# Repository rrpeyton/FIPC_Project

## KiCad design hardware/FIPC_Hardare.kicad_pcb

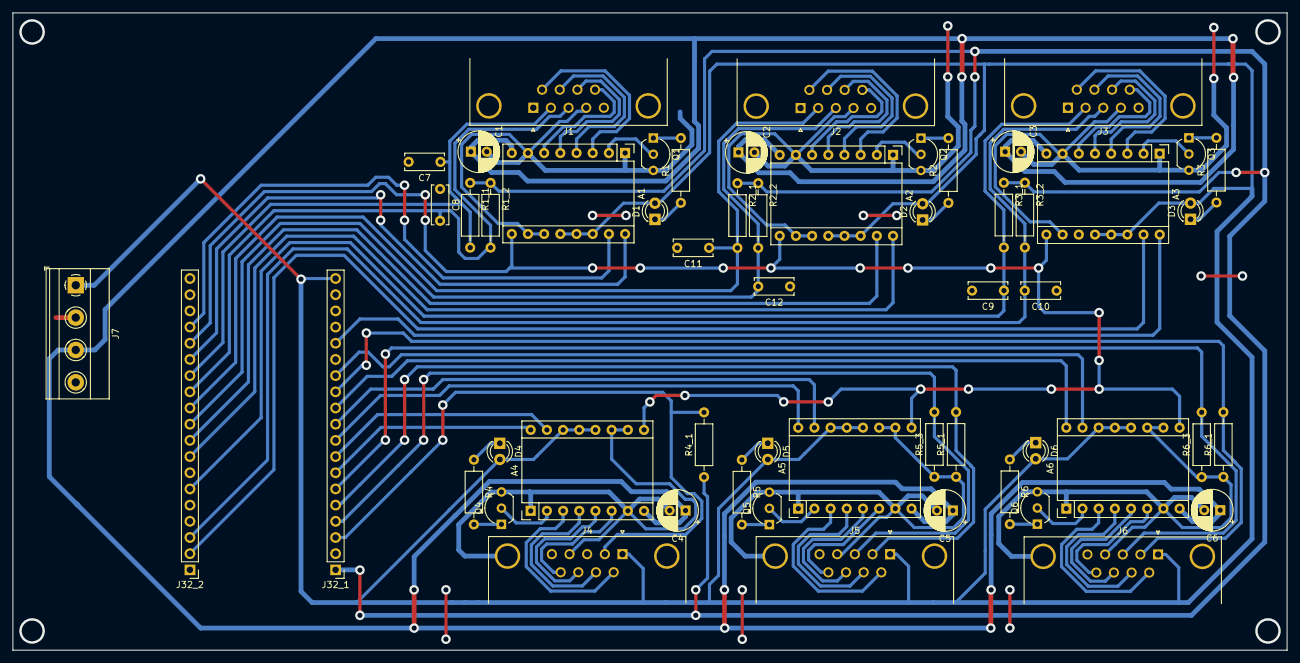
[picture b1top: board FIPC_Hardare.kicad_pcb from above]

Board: 2 copper layers, 200.0 x 100.0 mm, 56 parts (0 on the bottom side), 70 nets.

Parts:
A1, A3: Driver M1; Pololu_Breakout-16_15.2x20.3mm
A2: Driver M2; Pololu_Breakout-16_15.2x20.3mm
A4: Driver M4; Pololu_Breakout-16_15.2x20.3mm
A5: Driver M5; Pololu_Breakout-16_15.2x20.3mm
A6: Driver M6; Pololu_Breakout-16_15.2x20.3mm
C1, C2, C3, C4, C5, C6: 47uF; CP_Radial_D6.3mm_P2.50mm
C7, C8, C9, C10, C11, C12: 100nF; C_Disc_D6.0mm_W2.5mm_P5.00mm
D1, D2, D3, D4, D5, D6: LED; LED_D3.0mm
J1: DB9_M1; DSUB-9_Female_Horizontal_P2.77x2.84mm_EdgePinOffset4.94mm_H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
J2: DB9_M2; DSUB-9_Female_Horizontal_P2.77x2.84mm_EdgePinOffset4.94mm_H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
J3: DB9_M3; DSUB-9_Female_Horizontal_P2.77x2.84mm_EdgePinOffset4.94mm_H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
J4: DB9_M4; DSUB-9_Female_Horizontal_P2.77x2.84mm_EdgePinOffset4.94mm_H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
J5: DB9_M5; DSUB-9_Female_Horizontal_P2.77x2.84mm_EdgePinOffset4.94mm_H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
J6: DB9_M6; DSUB-9_Female_Horizontal_P2.77x2.84mm_EdgePinOffset4.94mm_H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
J7: Screw_Terminal_01x04; TerminalBlock_Phoenix_MKDS-1,5-4-5.08_1x04_P5.08mm_Horizont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
J32_1, J32_2: ESP32-S; PinHeader_1x19_P2.54mm_Vertical
Q1, Q2, Q3, Q4, Q5, Q6: BC237; TO-92_Inline_Wide
R1, R2, R3, R4, R5, R6: 220; R_Axial_DIN0207_L6.3mm_D2.5mm_P10.16mm_Horizontal
R1_1, R1_2, R2_1, R2_2, R3_1, R3_2: 10k; R_Axial_DIN0207_L6.3mm_D2.5mm_P10.16mm_Horizontal
R4_1: 1k; R_Axial_DIN0207_L6.3mm_D2.5mm_P10.16mm_Horizontal
R5_1, R5_3, R6_1, R6_3: 1.8k; R_Axial_DIN0207_L6.3mm_D2.5mm_P10.16mm_Horizontal

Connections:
+3V3: J32_1.1, R1_1.1, R1_2.1, R2_1.1, R2_2.1, R3_1.1, R3_2.1, R4_1.1
+5V: A1.12, A1.13, A1.14, A2.12, A2.13, A2.14, A3.12, A3.13, A3.14, A4.12, A4.13, A4.14, A5.12, A5.13, A5.14, A6.12, A6.13, A6.14, D1.2, D2.2, D3.2, D4.2, D5.2, D6.2, J4.1, J5.1, J6.1, J7.1, J32_1.19
+12V: A1.8, A2.8, A3.8, A4.8, A5.8, A6.8, C1.1, C2.1, C3.1, C4.1, C5.1, C6.1, J7.3
EN: A1.9, A2.9, A3.9, A4.9, A5.9, A6.9, J32_2.15
FLT_1: A1.2, Q1.2
FLT_2: A2.2, Q2.2
FLT_3: A3.2, Q3.2
FLT_4: A4.2, Q4.2
FLT_5: A5.2, Q5.2
FLT_6: A6.2, Q6.2
GND: A1.1, A1.7, A1.10, A1.11, A2.1, A2.7, A2.10, A2.11, A3.1, A3.7, A3.10, A3.11, A4.1, A4.7, A4.10, A4.11, A5.1, A5.7, A5.10, A5.11, A6.1, A6.7, A6.10, A6.11, C1.2, C2.2, C3.2, C4.2, C5.2, C6.2, C7.2, C8.1, C9.2, C10.1, C11.2, C12.1, J1.0, J1.4, J2.0, J2.4, J3.0, J3.4, J4.0, J4.4, J5.0, J5.4, J6.0, J6.4, J7.2, J7.4, J32_2.1, J32_2.7, Q1.3, Q2.3, Q3.3, Q4.3, Q5.3, Q6.3, R5_1.1, R5_3.1, R6_1.1, R6_3.1
M1_A+: A1.3, J1.6
M1_A-: A1.4, J1.7
M1_B+: A1.5, J1.8
M1_B-: A1.6, J1.9
M1_DIR: A1.16, J32_2.14
M1_STEP: A1.15, J32_2.16
M1_SW1: C7.1, J1.2, J32_2.13, R1_1.2
M1_SW2: C8.2, J1.3, J32_2.12, R1_2.2
M2_A+: A2.3, J2.6
M2_A-: A2.4, J2.7
M2_B+: A2.5, J2.8
M2_B-: A2.6, J2.9
M2_DIR: A2.16, J32_2.8
M2_STEP: A2.15, J32_2.9
M2_SW1: C11.1, J2.2, J32_2.11, R2_1.2
M2_SW2: C12.2, J2.3, J32_2.10, R2_2.2
M3_A+: A3.3, J3.6
M3_A-: A3.4, J3.7
M3_B+: A3.5, J3.8
M3_B-: A3.6, J3.9
M3_DIR: A3.16, J32_1.15
M3_STEP: A3.15, J32_2.2
M3_SW1: C9.1, J3.2, J32_2.6, R3_1.2
M3_SW2: C10.2, J3.3, J32_2.3, R3_2.2
M4_A+: A4.3, J4.6
M4_A-: A4.4, J4.7
M4_B+: A4.5, J4.8
M4_B-: A4.6, J4.9
M4_DIR: A4.16, J32_1.7
M4_STEP: A4.15, J32_1.8
M4_SW1: J4.2, J32_1.3, R4_1.2
M5_A+: A5.3, J5.6
M5_A-: A5.4, J5.7
M5_B+: A5.5, J5.8
M5_B-: A5.6, J5.9
M5_DIR: A5.16, J32_1.9
M5_STEP: A5.15, J32_1.10
M5_SW1: J5.2, J32_1.5, R5_1.2
M5_SW2: J5.3, J32_1.4, R5_3.2
M6_A+: A6.3, J6.6
M6_A-: A6.4, J6.7
M6_B+: A6.5, J6.8
M6_B-: A6.6, J6.9
M6_DIR: A6.16, J32_1.11
M6_STEP: A6.15, J32_1.13
M6_SW1: J6.2, J32_1.12, R6_1.2
M6_SW2: J6.3, J32_1.6, R6_3.2
unnamed: D1.1, R1.1
unnamed: D2.1, R2.1
unnamed: D3.1, R3.1
unnamed: D4.1, R4.1
unnamed: D5.1, R5.1
unnamed: D6.1, R6.1
unnamed: Q1.1, R1.2
unnamed: Q2.1, R2.2
unnamed: Q3.1, R3.2
unnamed: Q4.1, R4.2
unnamed: Q5.1, R5.2
unnamed: Q6.1, R6.2

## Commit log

2020-12-28 Creo repositorio, carpeta "src"
2020-12-28 Creo repositorio, carpeta "doc"
2020-12-28 Creo repositorio, carpeta "python_emulator"
2020-12-28 Creo repositorio, carpeta "hardware"
2021-01-14 update emulator
